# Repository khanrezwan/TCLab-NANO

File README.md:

# TCLab-NANO
Through hole hobbyist friendly Arduino nano version of TCLab

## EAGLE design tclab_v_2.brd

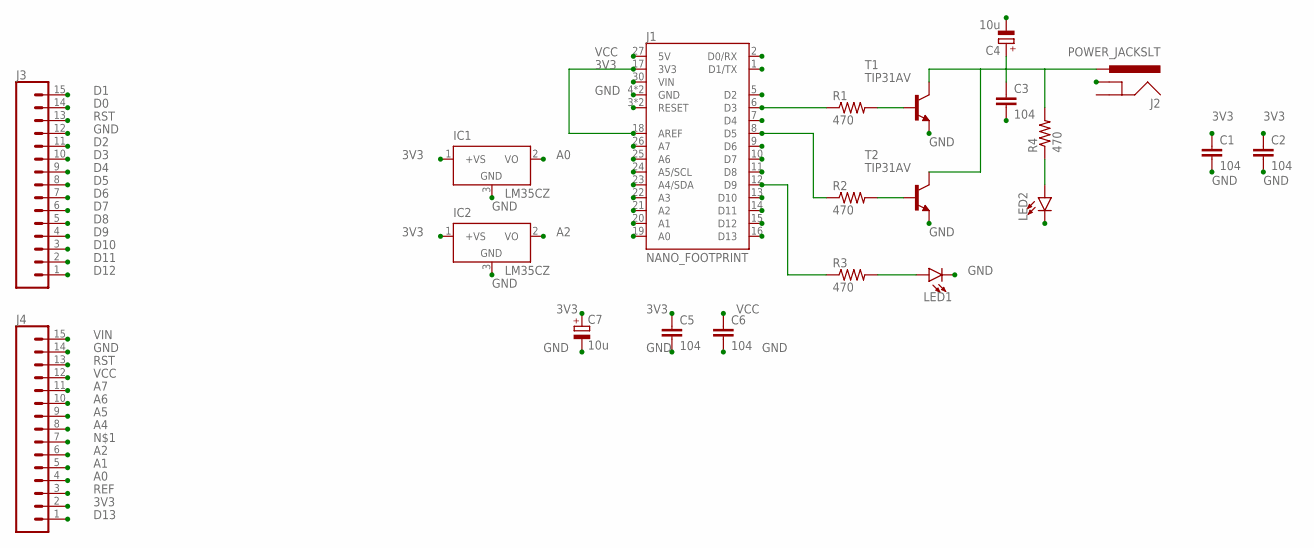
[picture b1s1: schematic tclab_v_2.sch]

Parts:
C1, C2, C3, C5, C6: 104; C025-025X050
C4, C7: 10u; E2,5-7
IC1, IC2: LM35CZ; TO92
J1: NANO_FOOTPRINT; NANO
J2: POWER_JACKSLT; POWER_JACK_SLOT
J3, J4: CONN_15; 1X15
LED1, LED2: LED5MM; LED_5MM
R1, R2, R3, R4: 470; 0204/7
T1, T2: TIP31AV; TO220AV

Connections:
3V3: C1.1, C2.1, C5.1, C7.+, IC1.1 (+VS), IC2.1 (+VS), J1.17 (3V3), J1.18 (AREF), J4.2
A0: IC1.2 (VO), J1.19 (A0), J4.4
A1: J1.20 (A1), J4.5
A2: IC2.2 (VO), J1.21 (A2), J4.6
A4: J1.23 (A4/SDA), J4.8
A5: J1.24 (A5/SCL), J4.9
A6: J1.25 (A6), J4.10
A7: J1.26 (A7), J4.11
D0: J1.2 (D0/RX), J3.14
D1: J1.1 (D1/TX), J3.15
D2: J1.5 (D2), J3.11
D3: J1.6 (D3), J3.10, R1.1
D4: J1.7 (D4), J3.9
D5: J1.8 (D5), J3.8, R2.1
D6: J1.9 (D6), J3.7
D7: J1.10 (D7), J3.6
D8: J1.11 (D8), J3.5
D9: J1.12 (D9), J3.4, R3.1
D10: J1.13 (D10), J3.3
D11: J1.14 (D11), J3.2
D12: J1.15 (D12), J3.1
D13: J1.16 (D13), J4.1
GND: C1.2, C2.2, C3.2, C4.-, C5.2, C6.2, C7.-, IC1.3 (GND), IC2.3 (GND), J1.4 (GND), J1.29 (GND), J2.GND@1 (GNDBREAK), J3.12, J4.14, LED1.K (C), LED2.K (C), T1.3 (E), T2.3 (E)
unnamed: J1.22 (A3), J4.7
unnamed: LED1.A, R3.2
unnamed: R2.2, T2.1 (B)
unnamed: R1.2, T1.1 (B)
unnamed: C3.1, C4.+, J2.PWR, R4.2, T1.2 (C), T2.2 (C)
unnamed: LED2.A, R4.1
REF: J4.3
RST: J1.3 (RESET), J1.28 (RESET), J3.13, J4.13
VCC: C6.1, J1.27 (5V), J4.12
VIN: J1.30 (VIN), J4.15

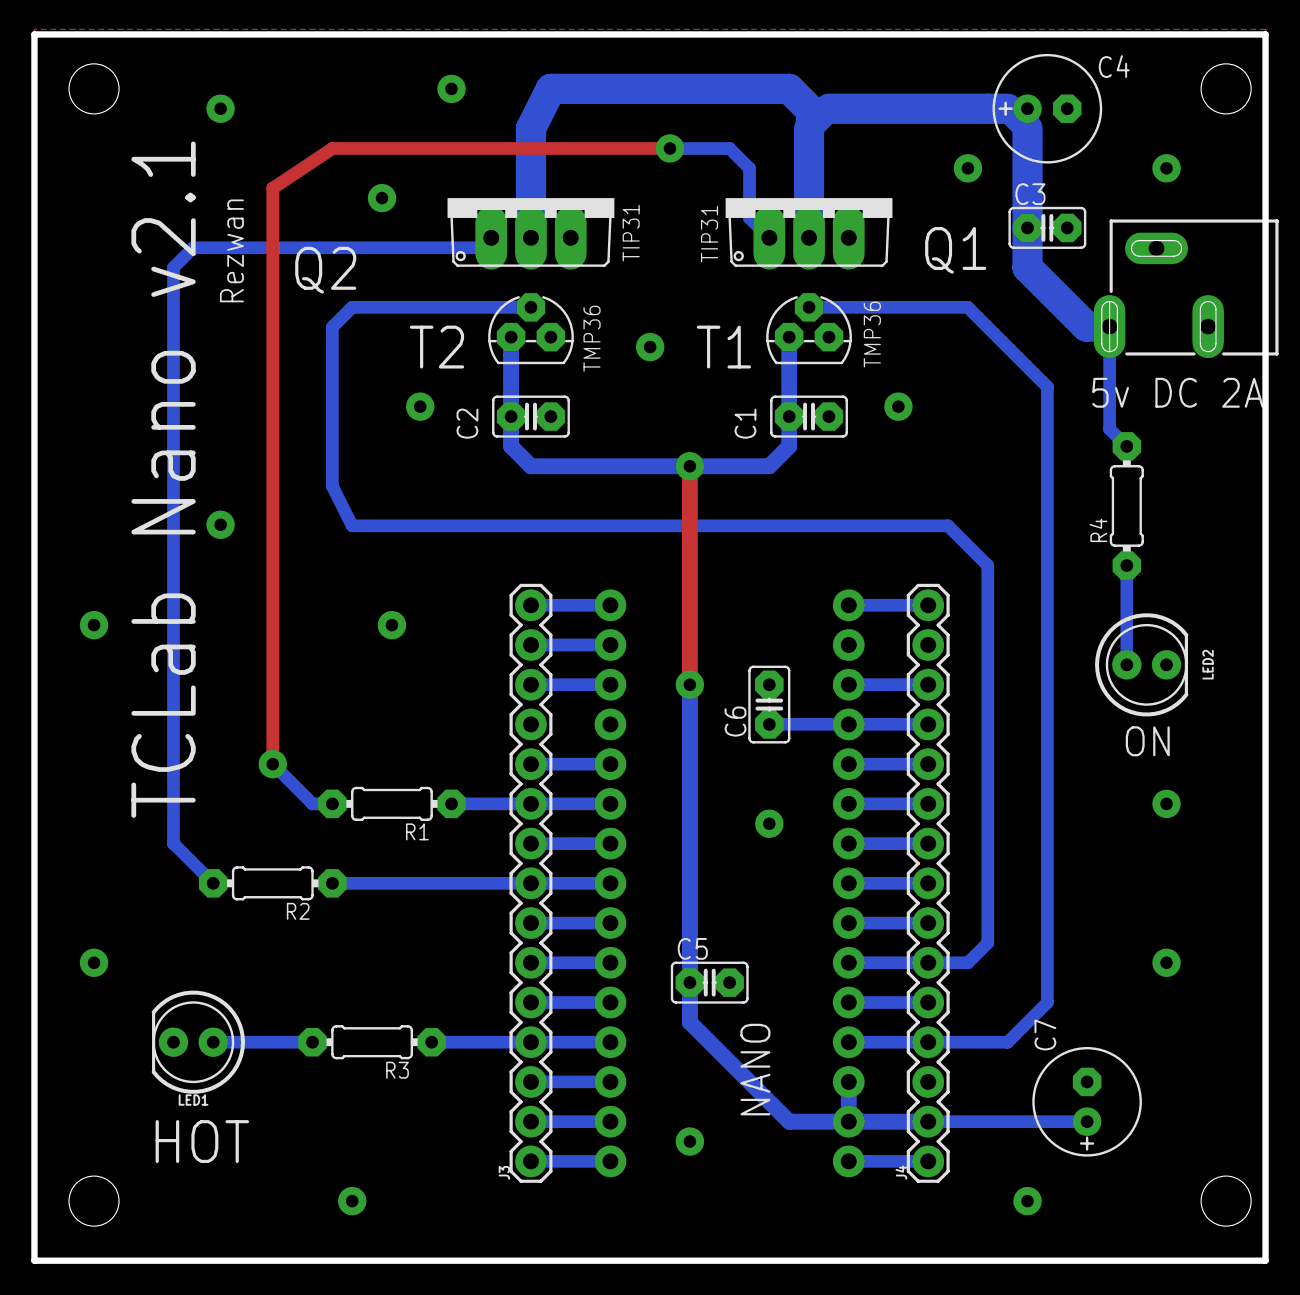
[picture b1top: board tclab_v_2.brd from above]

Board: 2 copper layers, 78.7 x 78.4 mm, 21 parts (0 on the bottom side), 32 nets.

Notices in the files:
parts and their libraries:
SparkFun-LED: Licensing: Creative Commons ShareAlike 4.0 International - https://creativecommons.org/licenses/by-sa/4.0
